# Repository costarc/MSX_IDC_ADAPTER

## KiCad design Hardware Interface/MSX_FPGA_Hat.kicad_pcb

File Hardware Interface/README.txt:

Note: Current master branch not ready for fabrication due to major changes in the design. I am re-writing the new VHDL Top level design to demux the interface signals and exposed the MSX BUS according to the new interface changes (view v2.0 notes below).

V2.01 - incompatible with previous cores.
- Removed U4_OE_n signal - this bus is not shared - can be grounded
- Fixed some silk placement
- Moved signals REFRESH,CS2 to own pins. This makes cores incompatible with version 2.0

v2.0 (With a few changes taken from Wondertang!)
- Added multiplex for MSX signals (shared GPIOS) to allow most MSX signals into the FPGA
- Added Audio circuitry from Wondertang (Luis Antoniosi project)
- Changed the open collector outputs to use transistor (/WAIt & /INT)
- Completely changed the PIN assigments - no compatible with previous boards

v1.6 (never sent for fabrication)
- Removed /CS1, CS2, CS12, RFSH, SOUND
- Moded U1 DIR control to jumper (allow enable by /RD or FPGA pin)
- Changed /WAIT & /INT to open collector using transistor

v1.5
- Added pull-up to MSX Data bus lines
- Added missing ground to LM1117
- Fixed bug (changed to 5V) in pull up on wait/int/busdir signals 

v1.4
- Added pull-up to all bus lines input to FPGA (4 x resistor network)
- Added RESET button (reset the MSX)

v1.3
- Updated edge connector (footprint) again, as per MSX standard for edge connector measures
- Moved RFSH & SOUNDIN to Jumper J1 (& removed previous jumpers J3/J4)
- Routed soundin & added R10
- Update silk with new retro games pictures

v1.2
- Changed footprint of PCB to 64mm in the base of cartridge as it was way too tight to insert
- Adde schotky diodes to MSX Input isgnals (Intt/Wait) to have the effect of open collector to isolate these signals from the FPGA when not actively driving them
- Added option to use MSX to power the interface (converted 5V to 3.3v via LD117)

v1.1
- Removed unnecessary xnor gate and jumpers
- Added other jumper to select signals to present to FPGA due to liitations in GPIO pins
- Changed pinout layout to support also Terasic DE0 

v1.0
- Initial version for Terasic DE1

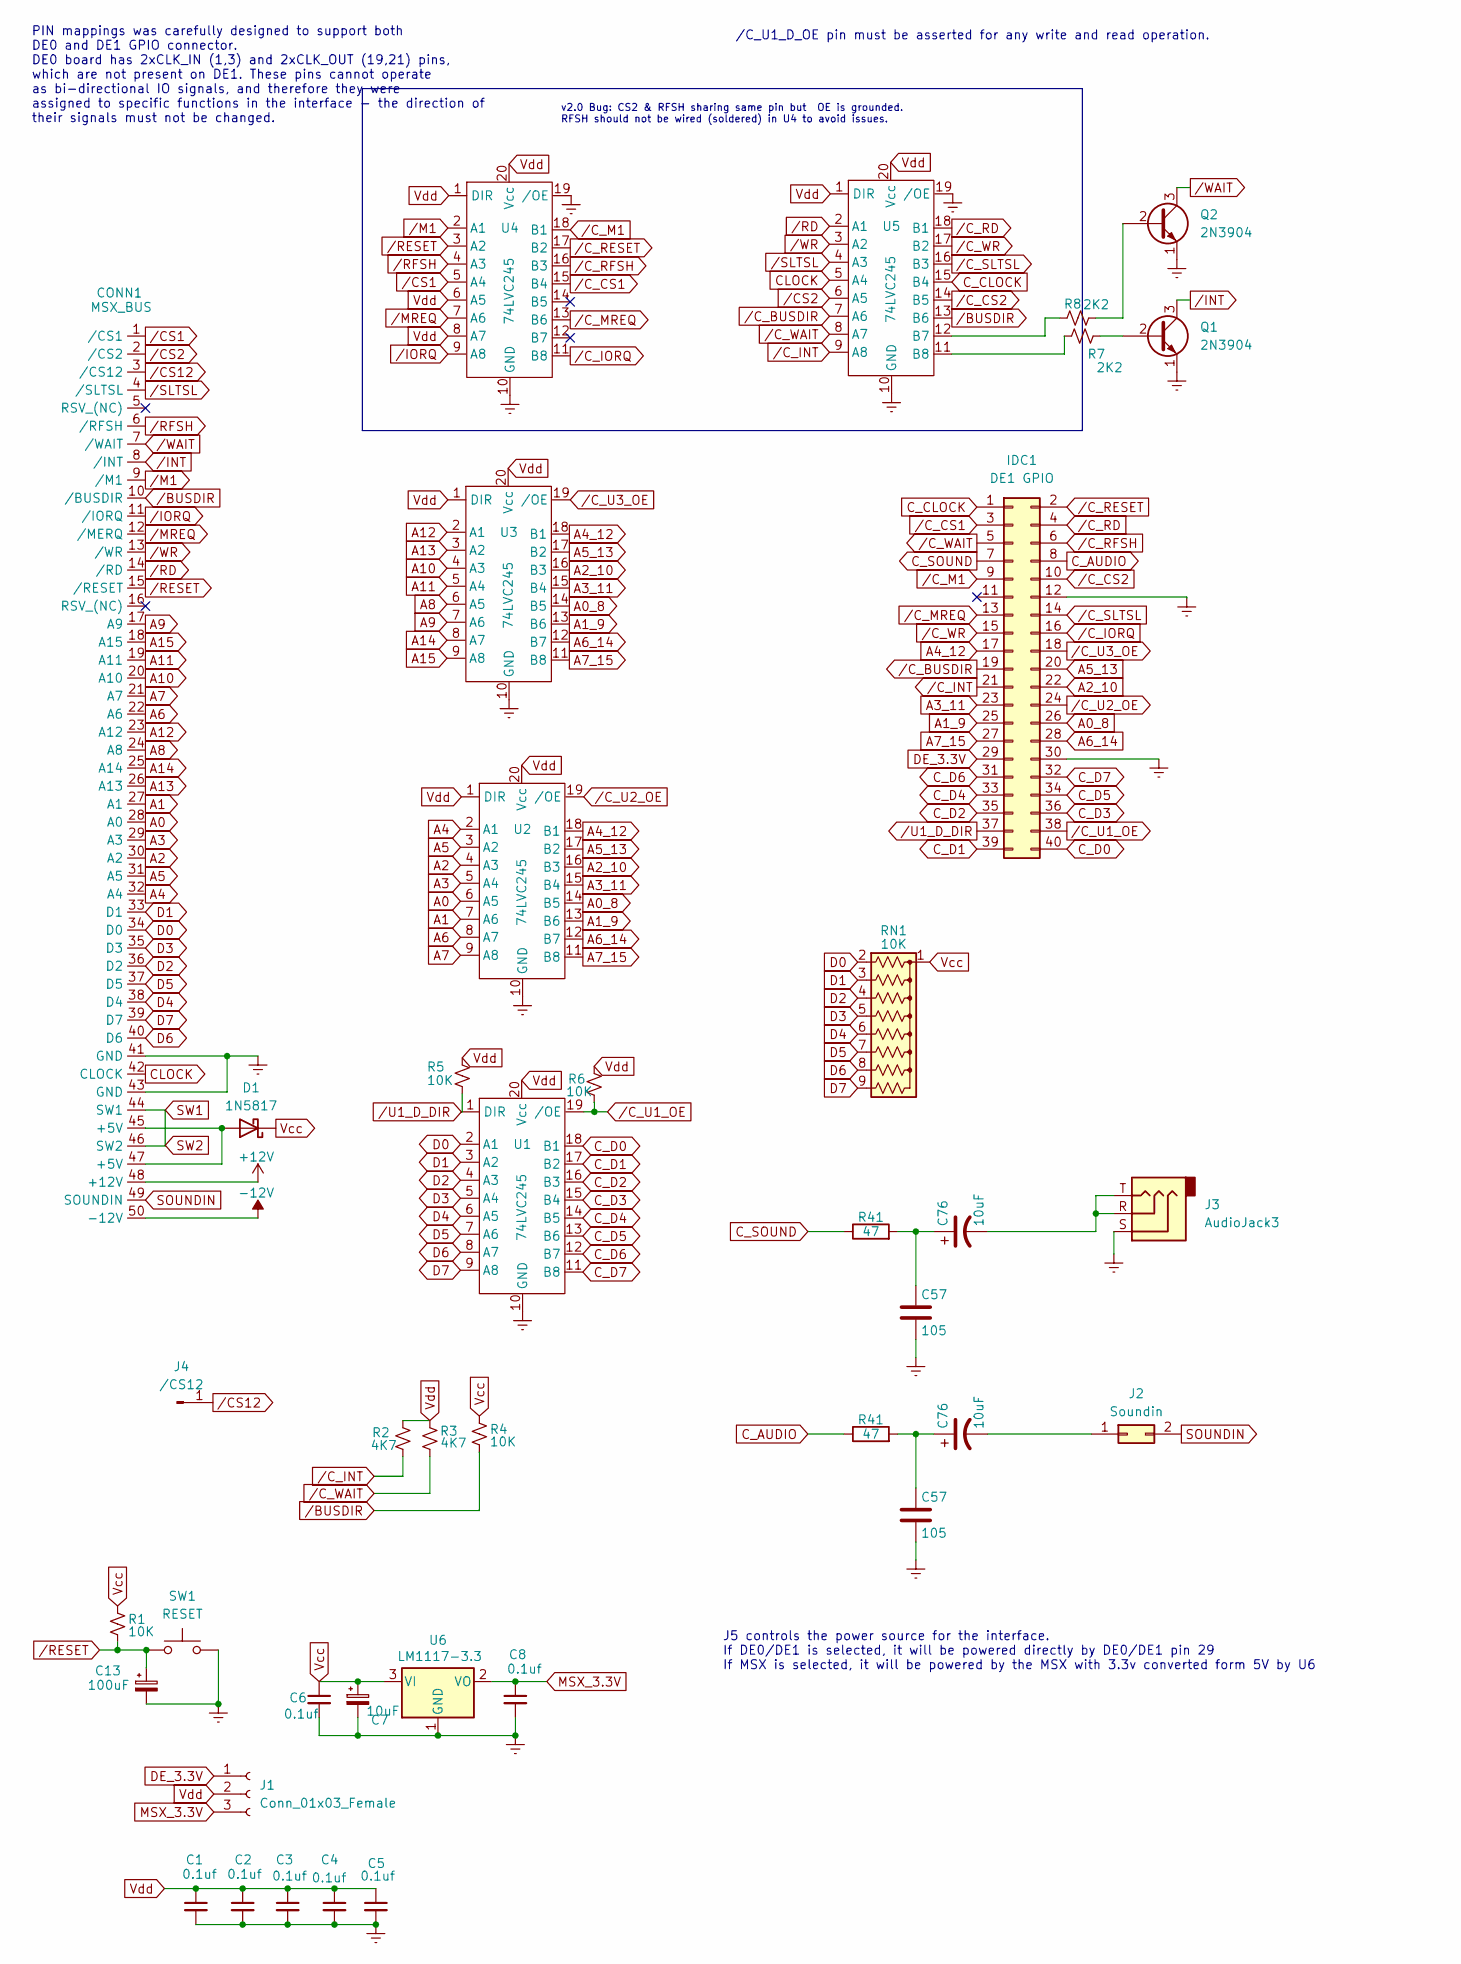
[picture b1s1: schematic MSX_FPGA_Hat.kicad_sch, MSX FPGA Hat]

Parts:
C1, C2, C3, C4, C5, C6, C8: 0.1uf; C_Disc_D3.0mm_W1.6mm_P2.50mm
C7, C76: 10uF; CP_Radial_D5.0mm_P2.00mm
C13: 100uF; CP_Radial_D5.0mm_P2.00mm
C57: 105; C_Disc_D5.0mm_W2.5mm_P2.50mm
CONN1: MSX_BUS; MSX_CART_SW_Official
D1: 1N5817; D_DO-41_SOD81_P10.16mm_Horizontal
IDC1: DE1 GPIO; PinHeader_2x20_P2.54mm_Vertical
J1: Conn_01x03_Female; PinHeader_1x03_P2.54mm_Vertical
J2: Soundin; PinHeader_2x01_P2.54mm_Vertical
J3: AudioJack3; Jack_3.5mm_CUI_SJ1-3533NG_Horizontal
J4: /CS12; PinHeader_1x01_P2.54mm_Vertical
Q1, Q2: 2N3904; TO-92_Inline
R1, R4, R5, R6: 10K; R_Axial_DIN0207_L6.3mm_D2.5mm_P10.16mm_Horizontal
R2, R3: 4K7; R_Axial_DIN0207_L6.3mm_D2.5mm_P10.16mm_Horizontal
R7, R8: 2K2; R_Axial_DIN0207_L6.3mm_D2.5mm_P10.16mm_Horizontal
R41: 47; R_Axial_DIN0207_L6.3mm_D2.5mm_P10.16mm_Horizontal
RN1: 10K; R_Array_SIP9
SW1: RESET; SW_Tactile_SKHH_Angled
U1, U2, U3, U4, U5: 74LVC245; DIP-20_W7.62mm
U6: LM1117-3.3; SOT-223-3_TabPin2

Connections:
+12V: CONN1.48 (+12V)
-12V: CONN1.50 (-12V)
A0: CONN1.28 (A0), U2.6 (A5)
A0_8: IDC1.26, U2.14 (B5), U3.14 (B5)
A1: CONN1.27 (A1), U2.7 (A6)
A1_9: IDC1.25, U2.13 (B6), U3.13 (B6)
A2: CONN1.30 (A2), U2.4 (A3)
A2_10: IDC1.22, U2.16 (B3), U3.16 (B3)
A3: CONN1.29 (A3), U2.5 (A4)
A3_11: IDC1.23, U2.15 (B4), U3.15 (B4)
A4: CONN1.32 (A4), U2.2 (A1)
A4_12: IDC1.17, U2.18 (B1), U3.18 (B1)
A5: CONN1.31 (A5), U2.3 (A2)
A5_13: IDC1.20, U2.17 (B2), U3.17 (B2)
A6: CONN1.22 (A6), U2.8 (A7)
A6_14: IDC1.28, U2.12 (B7), U3.12 (B7)
A7: CONN1.21 (A7), U2.9 (A8)
A7_15: IDC1.27, U2.11 (B8), U3.11 (B8)
A8: CONN1.24 (A8), U3.6 (A5)
A9: CONN1.17 (A9), U3.7 (A6)
A10: CONN1.20 (A10), U3.4 (A3)
A11: CONN1.19 (A11), U3.5 (A4)
A12: CONN1.23 (A12), U3.2 (A1)
A13: CONN1.26 (A13), U3.3 (A2)
A14: CONN1.25 (A14), U3.8 (A7)
A15: CONN1.18 (A15), U3.9 (A8)
CLOCK: CONN1.42 (CLOCK), U5.5 (A4)
C_AUDIO: IDC1.8; also elsewhere on the board
C_CLOCK: IDC1.1, U5.15 (B4)
C_D0: IDC1.40, U1.18 (B1)
C_D1: IDC1.39, U1.17 (B2)
C_D2: IDC1.35, U1.16 (B3)
C_D3: IDC1.36, U1.15 (B4)
C_D4: IDC1.33, U1.14 (B5)
C_D5: IDC1.34, U1.13 (B6)
C_D6: IDC1.31, U1.12 (B7)
C_D7: IDC1.32, U1.11 (B8)
C_SOUND: IDC1.7; also elsewhere on the board
D0: CONN1.34 (D0), RN1.2 (R1), U1.2 (A1)
D1: CONN1.33 (D1), RN1.3 (R2), U1.3 (A2)
D2: CONN1.36 (D2), RN1.4 (R3), U1.4 (A3)
D3: CONN1.35 (D3), RN1.5 (R4), U1.5 (A4)
D4: CONN1.38 (D4), RN1.6 (R5), U1.6 (A5)
D5: CONN1.37 (D5), RN1.7 (R6), U1.7 (A6)
D6: CONN1.40 (D6), RN1.8 (R7), U1.8 (A7)
D7: CONN1.39 (D7), RN1.9 (R8), U1.9 (A8)
DE_3.3V: IDC1.29, J1.1
GNDREF: C1.2, C2.2, C3.2, C4.2, C5.2, C6.2, C7.2, C8.2, C13.2, CONN1.41 (GND), CONN1.43 (GND), IDC1.12, IDC1.30, J3.S, Q1.1 (E), Q2.1 (E), SW1.2, U1.10 (GND), U2.10 (GND), U3.10 (GND), U4.10 (GND), U4.19 (/OE), U5.10 (GND), U5.19 (/OE), U6.1 (GND); also elsewhere on the board
MSX_3.3V: C8.1, J1.3, U6.2 (VO)
unnamed 51: J3.R, J3.T; also elsewhere on the board
unnamed: CONN1.45 (+5V), CONN1.47 (+5V), D1.2 (A)
unnamed 53: J2.1; also elsewhere on the board
unnamed: Q1.2 (B), R7.1
unnamed: Q2.2 (B), R8.1
unnamed: R8.2, U5.12 (B7)
unnamed: R7.2, U5.11 (B8)
SOUNDIN: CONN1.49 (SOUNDIN), J2.2
SW1: CONN1.44 (SW1), CONN1.46 (SW2)
Vcc: C6.1, C7.1, D1.1 (K), R1.1, R4.1, RN1.1 (common), U6.3 (VI)
Vdd: C1.1, C2.1, C3.1, C4.1, C5.1, J1.2, R2.1, R3.1, R5.1, R6.1, U1.20 (Vcc), U2.1 (DIR), U2.20 (Vcc), U3.1 (DIR), U3.20 (Vcc), U4.1 (DIR), U4.6 (A5), U4.8 (A7), U4.20 (Vcc), U5.1 (DIR), U5.20 (Vcc)
/BUSDIR: CONN1.10 (/BUSDIR), R4.2, U5.13 (B6)
/CS1: CONN1.1 (/CS1), U4.5 (A4)
/CS2: CONN1.2 (/CS2), U5.6 (A5)
/CS12: CONN1.3 (/CS12), J4.1
/C_BUSDIR: IDC1.19, U5.7 (A6)
/C_CS1: IDC1.3, U4.15 (B4)
/C_CS2: IDC1.10, U5.14 (B5)
/C_INT: IDC1.21, R2.2, U5.9 (A8)
/C_IORQ: IDC1.16, U4.11 (B8)
/C_M1: IDC1.9, U4.18 (B1)
/C_MREQ: IDC1.13, U4.13 (B6)
/C_RD: IDC1.4, U5.18 (B1)
/C_RESET: IDC1.2, U4.17 (B2)
/C_RFSH: IDC1.6, U4.16 (B3)
/C_SLTSL: IDC1.14, U5.16 (B3)
/C_U1_OE: IDC1.38, R6.2, U1.19 (/OE)
/C_U2_OE: IDC1.24, U2.19 (/OE)
/C_U3_OE: IDC1.18, U3.19 (/OE)
/C_WAIT: IDC1.5, R3.2, U5.8 (A7)
/C_WR: IDC1.15, U5.17 (B2)
/INT: CONN1.8 (/INT), Q1.3 (C)
/IORQ: CONN1.11 (/IORQ), U4.9 (A8)
/M1: CONN1.9 (/M1), U4.2 (A1)
/MREQ: CONN1.12 (/MERQ), U4.7 (A6)
/RD: CONN1.14 (/RD), U5.2 (A1)
/RESET: C13.1, CONN1.15 (/RESET), R1.2, SW1.1, U4.3 (A2)
/RFSH: CONN1.6 (/RFSH), U4.4 (A3)
/SLTSL: CONN1.4 (/SLTSL), U5.4 (A3)
/U1_D_DIR: IDC1.37, R5.2, U1.1 (DIR)
/WAIT: CONN1.7 (/WAIT), Q2.3 (C)
/WR: CONN1.13 (/WR), U5.3 (A2)

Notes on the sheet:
PIN mappings was carefully designed to support both DE0 and DE1 GPIO connector. DE0 board has 2xCLK_IN (1,3) and 2xCLK_OUT (19,21) pins, which are not present on DE1. These pins cannot operate as bi-directional IO signals, and therefore they were assigned to specific functions in the interface - th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
/C_U1_D_OE pin must be asserted for any write and read operation.
J5 controls the power source for the interface. If DE0/DE1 is selected, it will be powered directly by DE0/DE1 pin 29 If MSX is selected, it will be powered by the MSX with 3.3v converted form 5V by U6
v2.0 Bug: CS2 & RFSH sharing same pin but OE is grounded. RFSH should not be wired (soldered) in U4 to avoid issues.

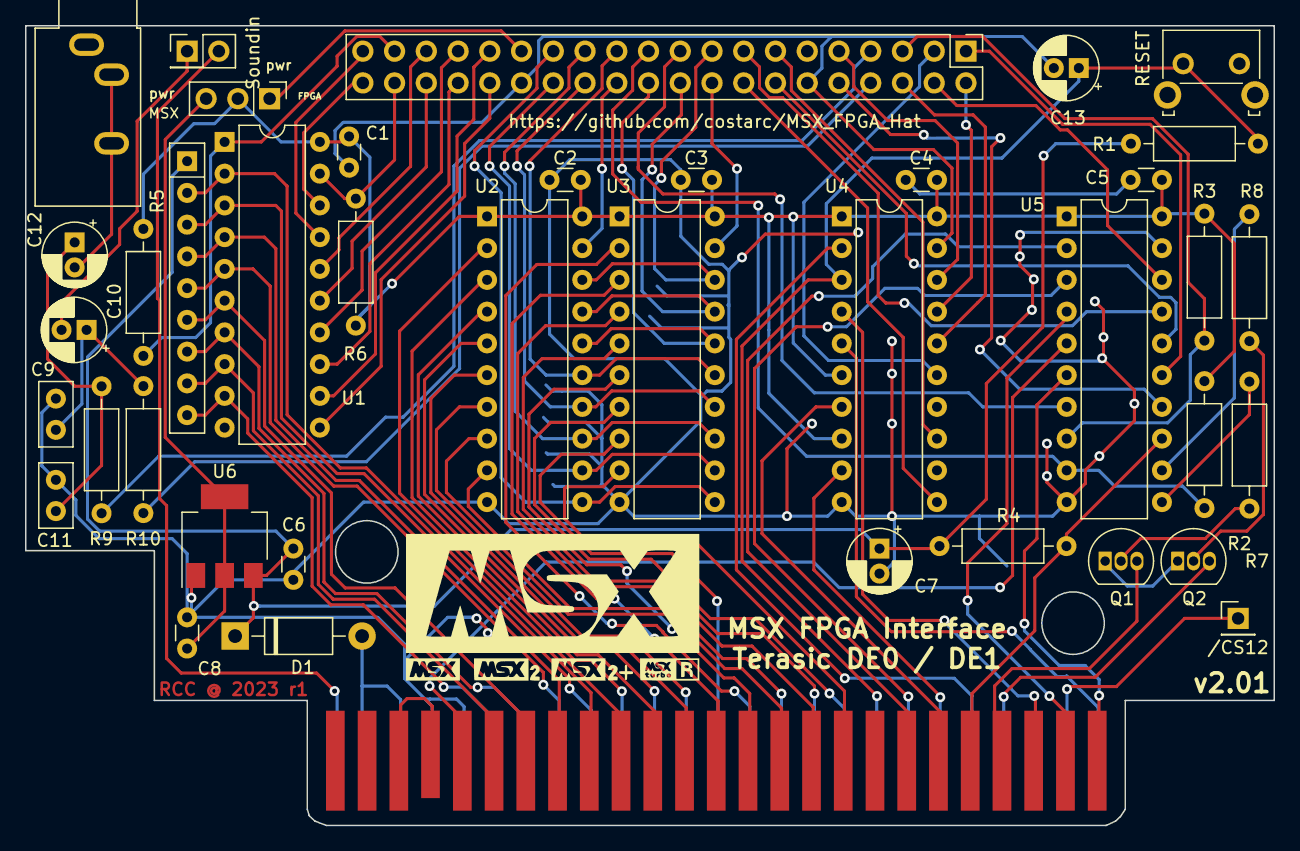
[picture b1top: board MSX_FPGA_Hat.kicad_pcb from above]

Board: 2 copper layers, 99.9 x 64.0 mm, 40 parts (0 on the bottom side), 91 nets.

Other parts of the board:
C9, C11: 105; C_Disc_D5.0mm_W2.5mm_P2.50mm
C10, C12: 10uF; CP_Radial_D5.0mm_P2.00mm
R9, R10: 47; R_Axial_DIN0207_L6.3mm_D2.5mm_P10.16mm_Horizontal

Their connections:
C_AUDIO: R10.1; also elsewhere on the board
C_SOUND: R9.1; also elsewhere on the board
GNDREF: C9.2, C11.2; also elsewhere on the board
unnamed: C9.1, C10.1, R10.2
unnamed: C11.1, C12.1, R9.2
unnamed 51: C12.2; also elsewhere on the board
unnamed 53: C10.2; also elsewhere on the board

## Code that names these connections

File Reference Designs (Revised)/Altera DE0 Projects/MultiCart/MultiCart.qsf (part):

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set_location_assignment PIN_W17 -to SLTSL_n
set_location_assignment PIN_U15 -to WR_n
set_location_assignment PIN_T15 -to IORQ_n
set_location_assignment PIN_W15 -to A4_12
set_location_assignment PIN_V15 -to U3_OE_n
set_location_assignment PIN_R16 -to BUSDIR_n
set_location_assignment PIN_AB9 -to A5_13
set_location_assignment PIN_T16 -to INT_n
set_location_assignment PIN_AA9 -to A2_10
set_location_assignment PIN_AA7 -to A3_11
set_location_assignment PIN_AB7 -to U2_OE_n
set_location_assignment PIN_T14 -to A1_9
set_location_assignment PIN_R14 -to A0_8
set_location_assignment PIN_U12 -to A7_15
set_location_assignment PIN_T12 -to A6_14
set_location_assignment PIN_R11 -to D[6]
set_location_assignment PIN_R12 -to D[7]
set_location_assignment PIN_U10 -to D[4]
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
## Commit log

2025-01-13 fixed typos in the schematic info text
2025-01-13 updated pdf with 2.01 schematic
2025-01-14 Reference Design (Revised) for MultiCart (incomplete)

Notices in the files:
Reference Designs (Revised)/Altera DE0 Projects/MultiCart/MultiCart.qsf:
Copyright (C) 1991-2013 Altera Corporation
